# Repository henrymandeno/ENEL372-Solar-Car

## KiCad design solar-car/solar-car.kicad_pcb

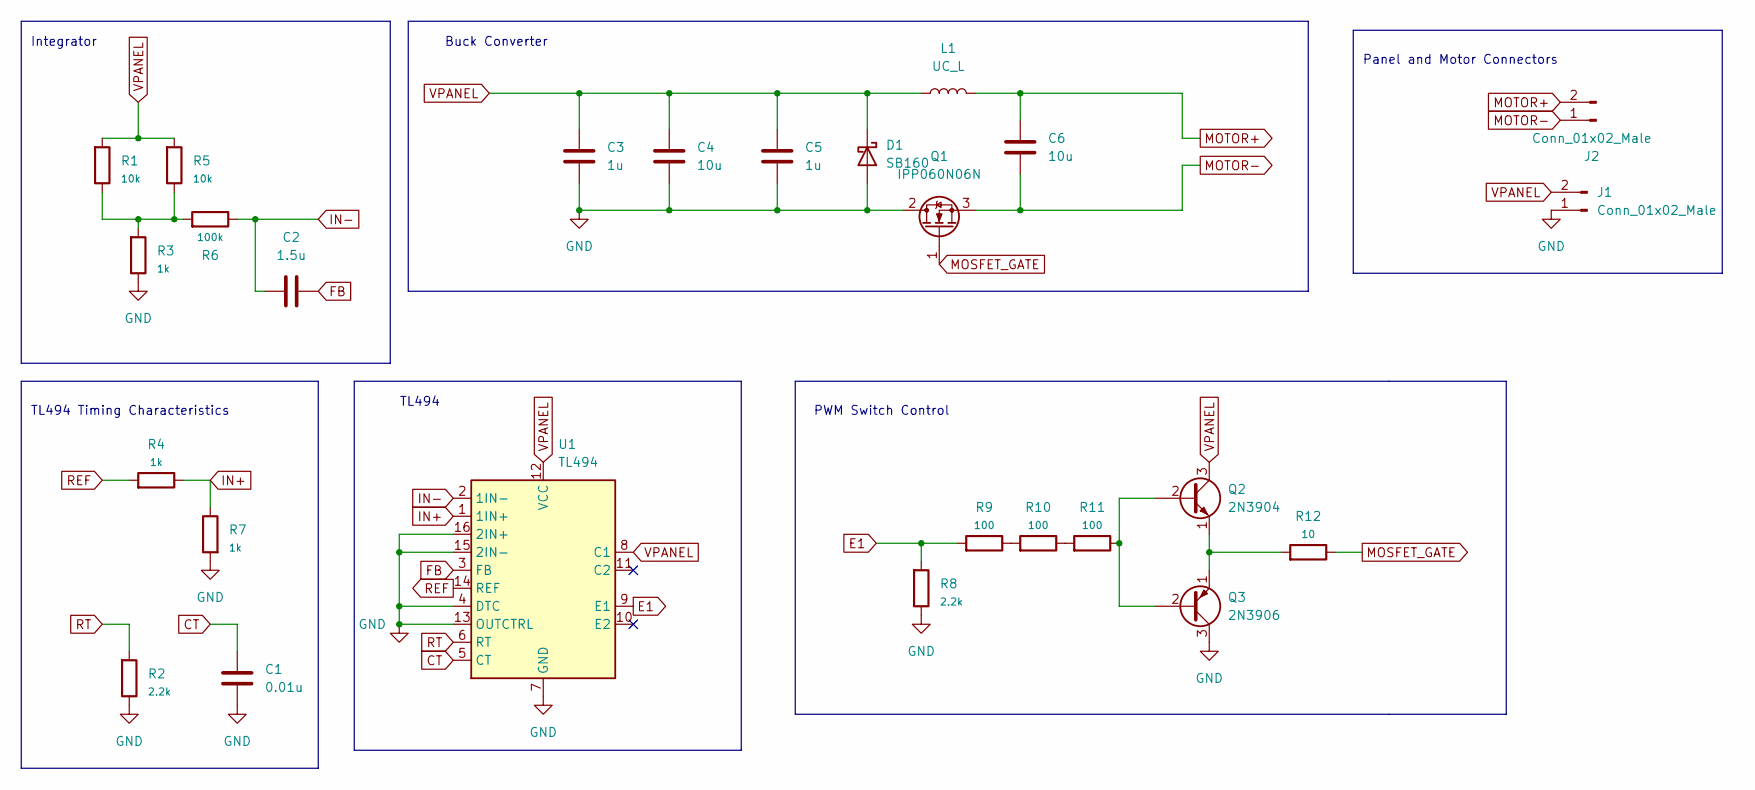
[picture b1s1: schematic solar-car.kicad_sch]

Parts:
C1: 0.01u; C_Rect_L7.0mm_W2.5mm_P5.00mm
C2: 1.5u; C_Rect_L7.0mm_W2.5mm_P5.00mm
C3, C5: 1u; C_Rect_L7.0mm_W2.5mm_P5.00mm
C4, C6: 10u; C_Rect_L7.0mm_W2.5mm_P5.00mm
D1: SB160; D_DO-41_SOD81_P10.16mm_Horizontal
J1, J2: Conn_01x02_Male; PinHeader_1x02_P2.54mm_Vertical
L1: UC_L; L_Axial_L16.0mm_D7.5mm_P20.32mm_Horizontal_Fastron_XHBCC
Q1: IPP060N06N; TO-220-3_Vertical
Q2: 2N3904; TO-92_Inline
Q3: 2N3906; TO-92_Inline
R1, R5: 10k; R_Axial_DIN0207_L6.3mm_D2.5mm_P2.54mm_Vertical
R2, R8: 2.2k; R_Axial_DIN0207_L6.3mm_D2.5mm_P2.54mm_Vertical
R3, R4, R7: 1k; R_Axial_DIN0207_L6.3mm_D2.5mm_P2.54mm_Vertical
R6: 100k; R_Axial_DIN0207_L6.3mm_D2.5mm_P2.54mm_Vertical
R9, R10, R11: 100; R_Axial_DIN0207_L6.3mm_D2.5mm_P2.54mm_Vertical
R12: 10; R_Axial_DIN0207_L6.3mm_D2.5mm_P2.54mm_Vertical
U1: TL494; DIP-16_W7.62mm

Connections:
CT: C1.1, U1.5 (CT)
E1: R8.1, R9.1, U1.9 (E1)
FB: C2.2, U1.3 (FB)
GND: C1.2, C3.2, C4.2, C5.2, D1.2 (A), J1.1, Q1.2 (D), Q3.3 (C), R2.2, R3.2, R7.1, R8.2, U1.4 (DTC), U1.7 (GND), U1.13 (OUTCTRL), U1.15 (2IN-), U1.16 (2IN+)
IN+: R4.2, R7.2, U1.1 (1IN+)
IN-: C2.1, R6.2, U1.2 (1IN-)
MOSFET_GATE: Q1.1 (G), R12.2
MOTOR+: C6.1, J2.2, L1.2
MOTOR-: C6.2, J2.1, Q1.3 (S)
unnamed: Q2.1 (E), Q3.1 (E), R12.1
unnamed: Q2.2 (B), Q3.2 (B), R11.2
unnamed: R1.2, R3.1, R5.2, R6.1
unnamed: R9.2, R10.1
unnamed: R10.2, R11.1
REF: R4.1, U1.14 (REF)
RT: R2.1, U1.6 (RT)
VPANEL: C3.1, C4.1, C5.1, D1.1 (K), J1.2, L1.1, Q2.3 (C), R1.1, R5.1, U1.8 (C1), U1.12 (VCC)

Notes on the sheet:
Panel and Motor Connectors
PWM Switch Control
TL494 Timing Characteristics
Buck Converter
TL494
Integrator

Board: 2 copper layers, 26 parts (0 on the bottom side), 17 nets, no tracks yet.

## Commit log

2022-10-04 Added KiCad files
